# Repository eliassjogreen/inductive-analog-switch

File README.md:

# Inductive Analog Switches

This library contains footprints and symbols for inductive analog keyboard
switches for use with the Texas Instruments LDC1312, LDC1314, LDC1612 and
LDC1614 inductance to digital converters.

Supported footprints for switches are currently PCB or plate mounted, LED or no
LED Cherry MX, Alps Matias or hybrid Cherry MX and Alps Matias.

## Requirements

- [KiCad](https://www.kicad.org/)
- [Python](https://www.python.org/)
  - `$ python -m pip install -r requirements.txt`

## Package

To generate the KiCad PCM package simply run the following command:

```sh
make
# Or:
make package
```

## Useful tools

- [Texas Instruments LDC Coil designer](https://webench.ti.com/wb5/LDC)

## Acknowledgements

A huge thank you goes out to
[keyswitch-kicad-library](https://github.com/perigoso/keyswitch-kicad-library)
from which i have borrowed some of the code to help generate the switch
footprints.

## Contributing

Contributions are very welcome! Just make sure to follow the rest of this
projects style as closely as possible and format with `make fmt`.

## License

This work is licensed under a
[Creative Commons Attribution-ShareAlike 4.0 International License](http://creativecommons.org/licenses/by-sa/4.0/).

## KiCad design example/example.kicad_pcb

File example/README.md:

# Example

This folder contains all of the relevant parts for an example PCB using the
inductive analog keyswitch footprints and symbols along with the LDC1314 or
LDC1614 inductance to digital converter. The example is a simple breakout board
for four switches and a SMD mounted LDC1314 IC.

## Requirements

- [KiCad](https://www.kicad.org/)
- [Python](https://www.python.org/)
- [Kikit](https://github.com/yaqwsx/KiKit)

## Fabrication

To generate gerbers for fabrication you will have to run one or all of the
makefile commands:

```sh
make
# Or one of the following:
make fab-jlcpcb
make fab-oshpark
make fab-pcbway
```

## License

This work is licensed under a
[Creative Commons Attribution-ShareAlike 4.0 International License](http://creativecommons.org/licenses/by-sa/4.0/).

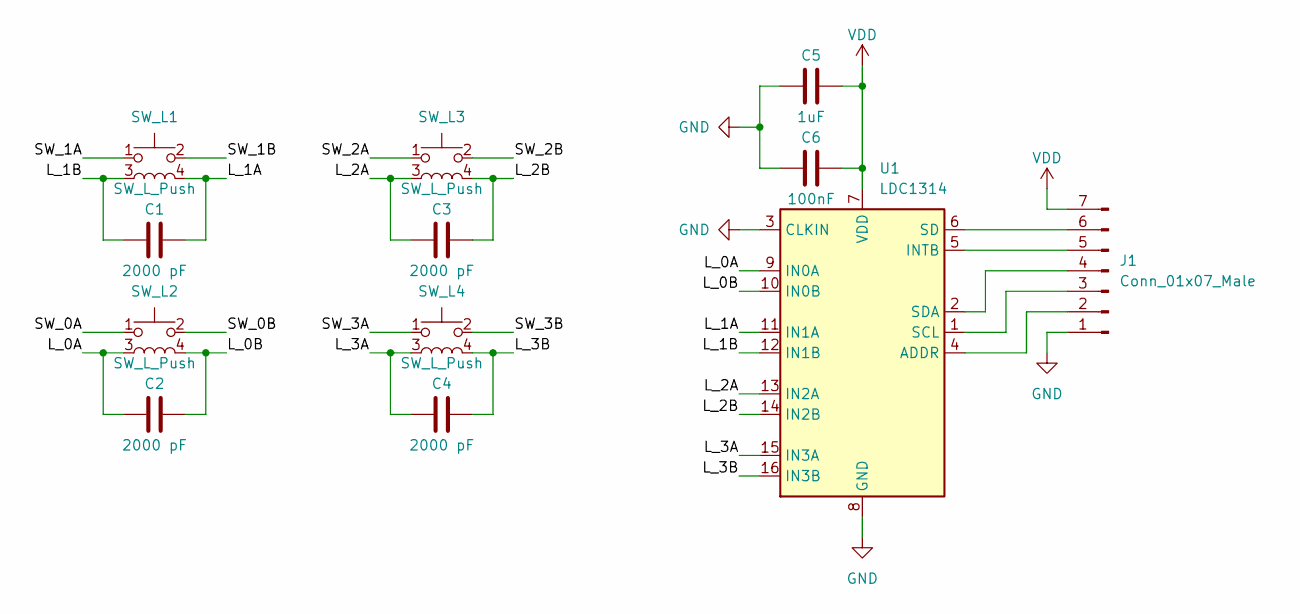
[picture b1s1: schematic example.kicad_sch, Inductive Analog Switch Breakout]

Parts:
C1, C2, C3, C4: 2000 pF; C_0805_2012Metric_Pad1.18x1.45mm_HandSolder
C5: 1uF; C_0805_2012Metric_Pad1.18x1.45mm_HandSolder
C6: 100nF; C_0805_2012Metric_Pad1.18x1.45mm_HandSolder
J1: Conn_01x07_Male; PinHeader_1x07_P2.54mm_Vertical
SW_L1, SW_L2, SW_L3, SW_L4: SW_L_Push; SW_L_Inductive_Cherry_MX_Alps_Matias_Plate
U1: LDC1314; WQFN-16-1EP_4x4mm_P0.5mm_EP2.6x2.6mm_ThermalVias

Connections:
/SW_0A: SW_L2.1
/SW_0B: SW_L2.2
/SW_1A: SW_L1.1
/SW_1B: SW_L1.2
/SW_2A: SW_L3.1
/SW_2B: SW_L3.2
/SW_3A: SW_L4.1
/SW_3B: SW_L4.2
/SW_L_0A: C2.1, SW_L2.3, U1.9 (IN0A)
/SW_L_0B: C2.2, SW_L2.4, U1.10 (IN0B)
/SW_L_1A: C1.2, SW_L1.4, U1.11 (IN1A)
/SW_L_1B: C1.1, SW_L1.3, U1.12 (IN1B)
/SW_L_2A: C3.1, SW_L3.3, U1.13 (IN2A)
/SW_L_2B: C3.2, SW_L3.4, U1.14 (IN2B)
/SW_L_3A: C4.1, SW_L4.3, U1.15 (IN3A)
/SW_L_3B: C4.2, SW_L4.4, U1.16 (IN3B)
GND: C5.1, C6.1, J1.1, U1.3 (CLKIN), U1.8 (GND), U1.17 (GND)
unnamed: J1.2, U1.4 (ADDR)
unnamed: J1.3, U1.1 (SCL)
unnamed: J1.4, U1.2 (SDA)
unnamed: J1.5, U1.5 (INTB)
unnamed: J1.6, U1.6 (SD)
VDD: C5.2, C6.2, J1.7, U1.7 (VDD)

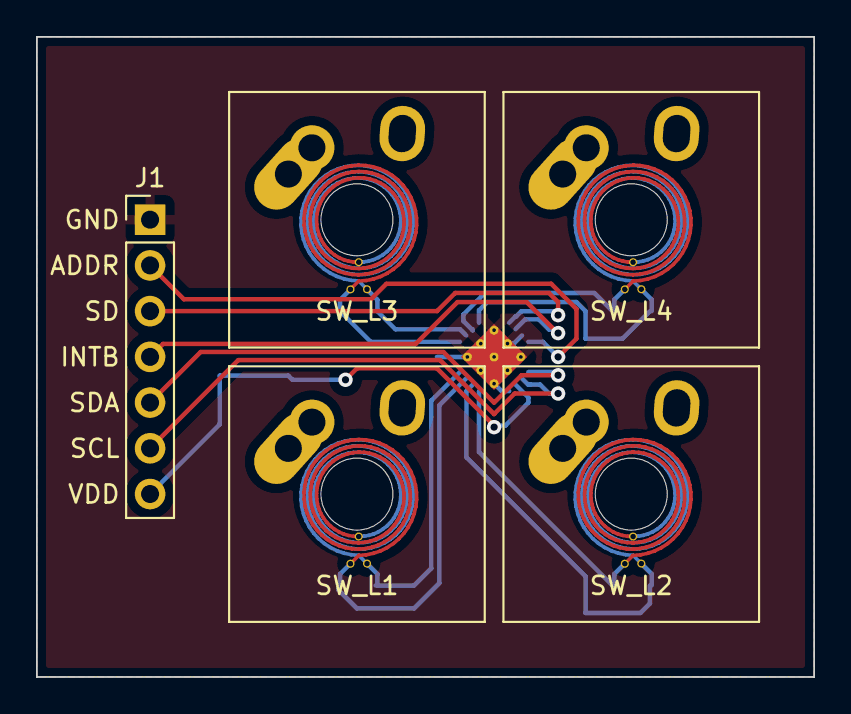
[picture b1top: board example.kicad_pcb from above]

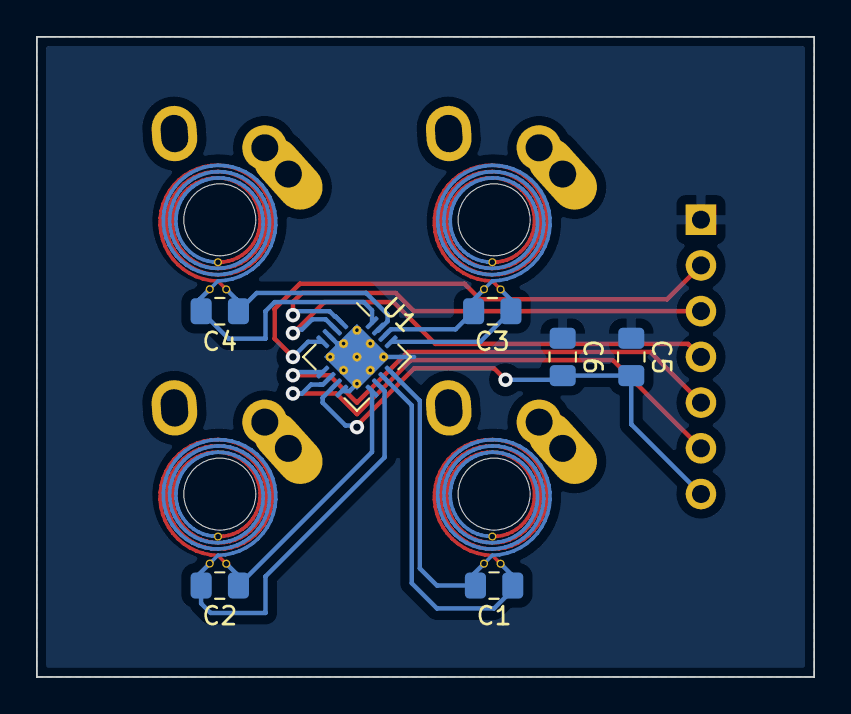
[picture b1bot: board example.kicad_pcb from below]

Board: 2 copper layers, 43.2 x 35.6 mm, 12 parts (7 on the bottom side), 15 nets.

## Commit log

2022-01-17 feat: initial commit
2022-01-17 feat: makefile
2022-01-17 feat: makefile, and start example project
2022-01-17 fix: symbol footprints
2022-04-08 feat: all scripts are now in python including pcm
2022-04-13 chore: delete gerbers
2022-04-13 feat: formatting
2022-04-13 kikit for automatic fab output of example
2022-04-15 docs: write README's and change paper size for example schematic
